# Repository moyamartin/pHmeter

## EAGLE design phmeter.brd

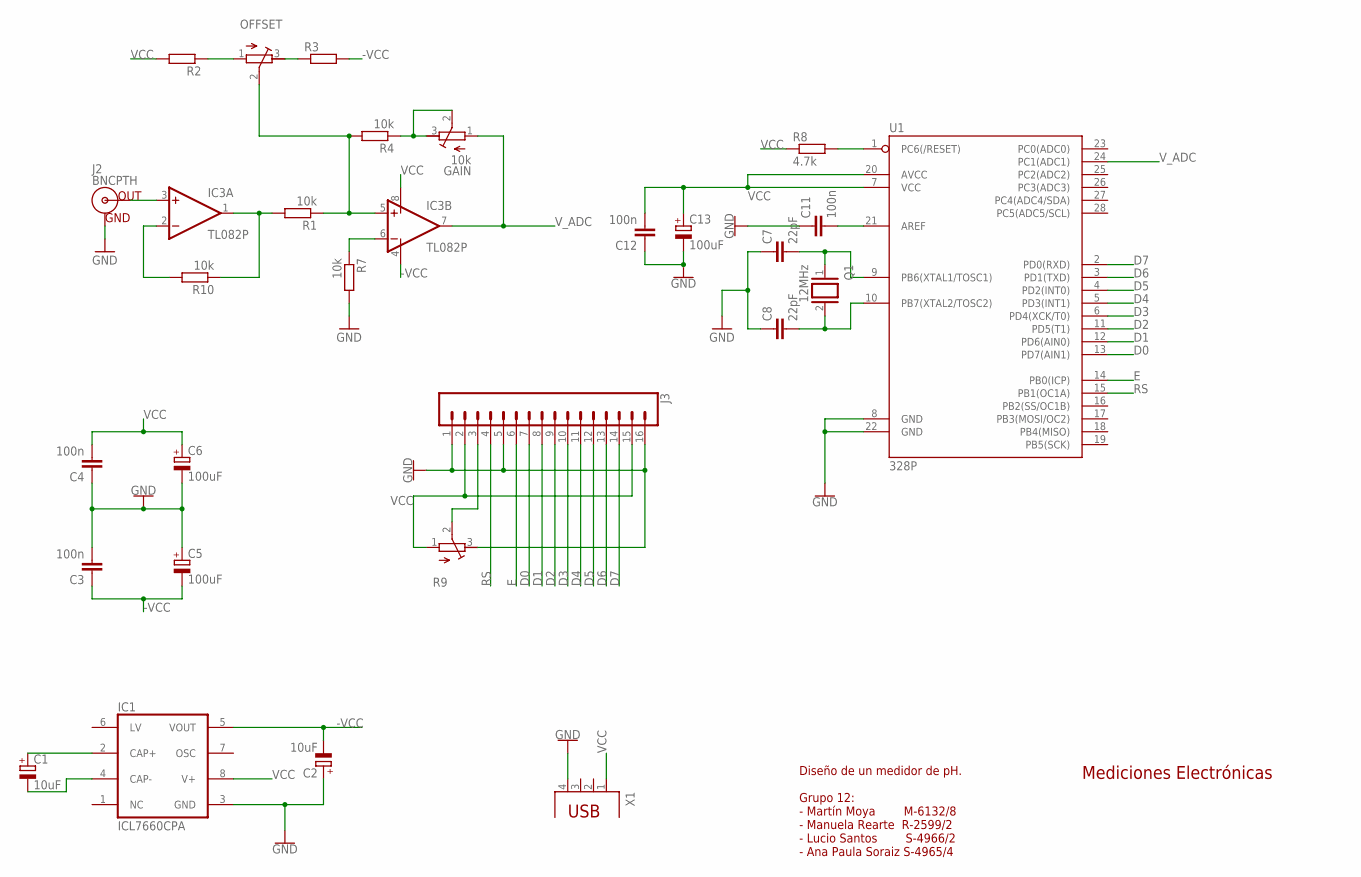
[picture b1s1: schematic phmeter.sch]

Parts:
C1, C2: 10uF; E1,8-4
C3, C4, C11, C12: 100n; C025-024X044
C5, C6, C13: 100uF; E1,8-4
C7, C8: 22pF; C025-024X044
GAIN: 10k; RTRIM64W
IC1: ICL7660CPA; DIL08
IC3: TL082P; DIL08
J2: BNCPTH; BNC
J3: CONN_16; 1X16
OFFSET: R-TRIMM64W; RTRIM64W
Q1: 12MHz; QS
R1, R4, R7, R10: 10k; 0207/10
R2, R3: R-EU_0207/10; 0207/10
R8: 4.7k; 0207/10
R9: R-TRIMM64W; RTRIM64W
U1: 328P; DIP28
X1: PN61729

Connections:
-VCC: C2.-, C3.1, C5.-, IC1.5 (VOUT), IC3.4 (V-), R3.2
D0: J3.7, U1.13 (PD7(AIN1))
D1: J3.8, U1.12 (PD6(AIN0))
D2: J3.9, U1.11 (PD5(T1))
D3: J3.10, U1.6 (PD4(XCK/T0))
D4: J3.11, U1.5 (PD3(INT1))
D5: J3.12, U1.4 (PD2(INT0))
D6: J3.13, U1.3 (PD1(TXD))
D7: J3.14, U1.2 (PD0(RXD))
E: J3.6, U1.14 (PB0(ICP))
GND: C2.+, C3.2, C4.1, C5.+, C6.-, C7.1, C8.1, C11.1, C12.1, C13.-, IC1.3 (GND), J2.GND, J3.1, J3.5, J3.16, R7.2, R9.3 (E), U1.8 (GND), U1.22 (GND), X1.4
unnamed: IC3.1 (OUT), R1.2, R10.1
unnamed: C1.+, IC1.2 (CAP+)
unnamed: GAIN.2 (S), GAIN.3 (E), R4.1
unnamed: IC3.6 (-IN), R7.1
unnamed: C1.-, IC1.4 (CAP-)
unnamed: OFFSET.3 (E), R3.1
unnamed: OFFSET.1 (A), R2.1
unnamed: C7.2, Q1.1, U1.9 (PB6(XTAL1/TOSC1))
unnamed: C8.2, Q1.2, U1.10 (PB7(XTAL2/TOSC2))
unnamed: J3.3, R9.2 (S)
unnamed: C11.2, U1.21 (AREF)
unnamed: R8.2, U1.1 (PC6(/RESET))
unnamed: IC3.3 (+IN), J2.S (OUT)
unnamed: IC3.2 (-IN), R10.2
RS: J3.4, U1.15 (PB1(OC1A))
VCC: C4.2, C6.+, C12.2, C13.+, IC1.8 (V+), IC3.8 (V+), J3.2, J3.15, R2.2, R8.1, R9.1 (A), U1.7 (VCC), U1.20 (AVCC), X1.1
V_ADC: GAIN.1 (A), IC3.7 (OUT), U1.24 (PC1(ADC1))
V_OFFSET: IC3.5 (+IN), OFFSET.2 (S), R1.1, R4.2

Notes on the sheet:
Diseño de un medidor de pH. Grupo 12: - Martín Moya M-6132/8 - Manuela Rearte R-2599/2 - Lucio Santos S-4966/2 - Ana Paula Soraiz S-4965/4
Mediciones Electrónicas

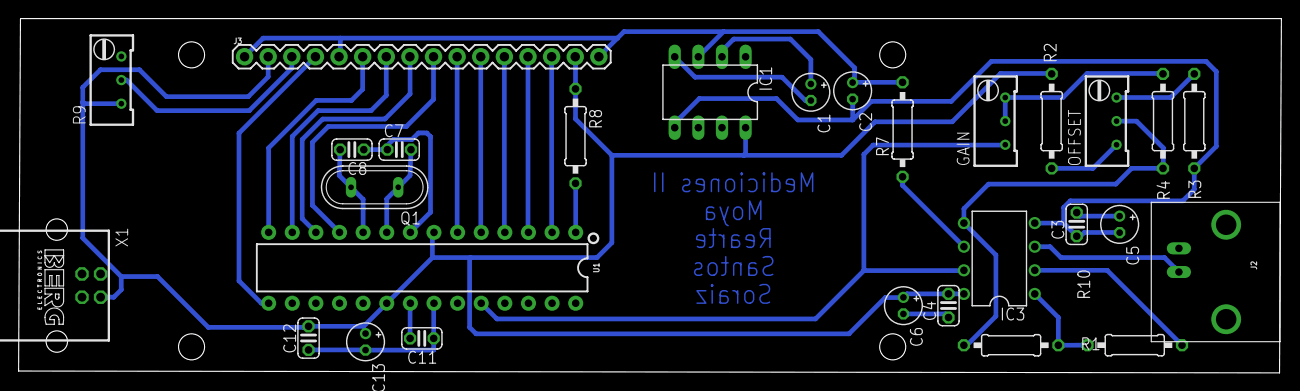
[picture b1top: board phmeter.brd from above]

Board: 2 copper layers, 135.8 x 38.1 mm, 28 parts (0 on the bottom side), 29 nets.

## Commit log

2017-10-22 Started Board Design
    Included FTDI + Atmel328P
2017-10-23 Added
2017-11-02 Pre-informe, code and simulation
2017-11-30 LCD - ADC Working - updated PCB
2017-12-01 Ended PCB design
    Generated PCB and it's pdf file. Ready to print.
2017-12-02 Finished Board Design
2017-12-04 Finished board, started documentation.

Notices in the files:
parts and their libraries:
SparkFun-Connectors: Licensing: Creative Commons ShareAlike 4.0 International - https://creativecommons.org/licenses/by-sa/4.0
